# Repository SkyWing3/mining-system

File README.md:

# Mining System

Central de operaciones para la manilla minera: ASP.NET Core 10, MySQL y React 19 + TypeScript y software Python para Raspberry Pi Zero 2 W. La Raspberry Pi 4 puede alojar la central. La interfaz utiliza blanco y la paleta `#DEC1AF`, `#491A06`, `#373946`, `#852A3B`, `#6C4B68`, en modo claro y sin gradientes.

La manilla lee el sensor de CO SEN0564 (mediante un ADS1115) y el termómetro infrarrojo MLX90614, muestra los valores en la OLED, avisa por LED RGB, buzzer y motor vibrador al superar sus umbrales, envía reportes predeterminados y mensajes de voz grabados con el INMP441, y recibe avisos de la central. Las lecturas llegan a la web **en tiempo real** por WebSocket.

## Ubuntu Server LTS con Docker

En la Raspberry Pi 4B con **Ubuntu Server LTS de 64 bits**, Docker y Docker Compose disponibles, ejecutar:

```sh
./start.sh
```

Si Docker requiere permisos de administrador, usar `sudo ./start.sh`. El script compila las imágenes, inicia la API y la web-app, espera sus comprobaciones de salud y muestra la dirección de acceso. Usar el mismo comando para actualizar tras cambiar el código.

Para detener la central conservando los datos: `./start.sh --down` (o `sudo ./start.sh --down`). `./start.sh --help` muestra las opciones.

Abrir **http://franco-rasp4.local**, usando el mDNS del servidor. Nginx redirige ambos WebSockets y la subida de voz; los datos, audios y sesiones se conservan en volúmenes. No hace falta crear `.env` ni instalar Node.js o .NET en el servidor.

Consultar [despliegue Docker](docs/docker.md) para configuración, actualizaciones, respaldos, mDNS y el contenedor opcional de la manilla.

## Desarrollo local

Requisitos: SDK .NET 10, Node.js 22.12+ (o 24+), npm y Python 3.10+ para el dispositivo y las pruebas.

Configurar primero MySQL según [docs/mysql.md](docs/mysql.md). Desde la raíz:

```sh
./scripts/dev.sh
```

Abrir **http://localhost:5173**. La API se ejecuta en **http://localhost:5080**. El primer acceso permite crear el administrador; no hay cuentas ni contraseñas predeterminadas. En accesos posteriores aparece el login. Ctrl+C detiene ambos servicios.

También se pueden iniciar por separado:

```sh
# Terminal 1
ASPNETCORE_ENVIRONMENT=Development dotnet run --project backend/backend.csproj --no-launch-profile

# Terminal 2
cd web-app
npm ci
npm run dev
```

Vite redirige `/api` y `/hubs` a la API para conservar las cookies en el mismo origen. Se puede cambiar el destino con `MINING_API_TARGET`. La configuración privada `launchSettings.json` del SDK puede contener puertos distintos; usar `--no-launch-profile`. Las migraciones se generan con la herramienta local: `dotnet tool restore && dotnet dotnet-ef migrations add Nombre --project backend/backend.csproj`.

## Flujo de uso

1. Crear el administrador desde la pantalla inicial.
2. En **Usuarios**, crear mineros y, si corresponde, supervisores. Las contraseñas tienen un mínimo de 10 caracteres.
3. En **Manillas**, registrar cada dispositivo, su zona y su minero. Cada minero puede tener una manilla activa. Guardar la credencial que se muestra una sola vez.
4. Copiar `device/config/settings.example.json` a `device/config/settings.json` y configurar la dirección de la central y esa credencial.
5. Iniciar el dispositivo o su simulador. Sus lecturas aparecen al instante en **En vivo**.
6. En la OLED, abrir **Mensajes**, seleccionar un reporte y confirmar **Enviar**, o abrir **Voz** para grabar un mensaje.
7. La central recibe el mensaje al instante en **Mensajes**, **Vista general** y, si es crítico, **Alertas**; las grabaciones aparecen en **Voz**.
8. Desde **Avisos** o desde la fila de una manilla se envía un aviso; su estado pasa de Pendiente a Entregado y Leído cuando el minero lo confirma con Enter.

| Rol | Permisos |
| --- | --- |
| Administrador | Monitoreo en vivo, mensajes, voz, avisos, revisión interna de alertas, manillas, gestión de usuarios, actividad y su cuenta. |
| Supervisor | Monitoreo en vivo, mensajes, voz, avisos, revisión interna de alertas, manillas, actividad y su cuenta. |
| Minero | Identidad del portador de la manilla; envía reportes y voz desde el dispositivo. No accede al panel de operaciones. |

Los reportes del menú son predeterminados: **Ayuda**, **Todo bien**, **Hay derrumbe**, **Presencia de gas**, **Compañero herido**, **Necesito evacuar**, **Necesito suministros** y **Saliendo de la mina**. La manilla envía además **Alarma de CO** y **Alarma de temperatura** cuando un sensor entra en peligro, con el valor medido. La web permite buscar (sin distinguir tildes), filtrar y exportar la página actual del historial. Marcar una alerta como revisada registra autor y fecha dentro de la central; no declara resuelto el incidente. Para comunicarse con el minero se usan los **avisos** predefinidos.

## Dispositivo y simulador

```sh
cd device
python3 -m venv .venv
.venv/bin/python -m pip install -r requirements.txt
cp -n config/settings.example.json config/settings.json
# Editar settings.json: connection.url y connection.api_key
.venv/bin/python -m src.main --simulate --config config/settings.json
```

El simulador abre una ventana con la OLED, los botones (flechas y Enter), el LED, el buzzer y el motor. Sus sensores generan lecturas **marcadas como simuladas**; las teclas `g` y `t` fuerzan un pico de CO o de calor para probar las alarmas. La voz simulada es un tono sintético: no usa el micrófono del equipo.

Ejemplo de conexión en la manilla:

```json
{
  "connection": {
    "url": "ws://192.168.1.20:5080/ws/device",
    "api_key": "COPIAR_LA_CREDENCIAL_GENERADA_EN_LA_WEB",
    "heartbeat_seconds": 20,
    "telemetry_seconds": 2,
    "outbox_path": "../state/outbox",
    "voice_outbox_path": "../state/voice"
  }
}
```

Las secciones `sensors`, `alerts` y `voice` son opcionales; sus valores por defecto están en `settings.example.json` y se describen en [OLED, sensores y alertas](docs/hardware/oled-buttons.md). Las rutas de las colas se resuelven respecto al archivo JSON. La URL de subida de voz se deriva de `connection.url` (`ws://host/ws/device` → `http://host/api/device/voice`).

Sin credencial configurada, el menú muestra **Sin configurar** y no declara mensajes enviados. Con credencial, cada mensaje, alarma automática y confirmación de aviso se guarda primero en una cola local de archivos JSON con escritura atómica: **Guardado en cola**. Solo pasa a **Enviado a central** cuando recibe confirmación persistida por el servidor. Si no hay red, permanece en cola y se reintenta al reconectar, incluso después de reiniciar el proceso. El identificador estable evita duplicados. Las grabaciones usan una cola equivalente de archivos WAV.

En hardware:

```sh
GPIOZERO_PIN_FACTORY=lgpio .venv/bin/python -m src.main --config config/settings.json
```

Consultar [OLED, sensores y alertas](docs/hardware/oled-buttons.md), [lista de componentes](docs/componentes.tex), [cableado completo](docs/conexiones.tex) y [diagrama de cableado](docs/imagenes/cableado.png). Para conectar otra Raspberry Pi, servir la central en su interfaz de red: `MINING_BIND_URL=http://0.0.0.0:5080 ./scripts/serve.sh`.

### Manilla con ESP32-S3

[`esp32-device/`](esp32-device/README.md) es el mismo software portado a un ESP32-S3 DevKitC con PlatformIO: mismo menú, alertas, colas y protocolo, sin ADS1115 (el SEN0564 usa el ADC interno). Se configura por la consola serie y la central no necesita cambios.

[`pcb/manilla-portadora/`](pcb/manilla-portadora/README.md) es la placa portadora de doble cara para esa DevKitC: carga y protección de la batería LiPo, elevador a 5 V, LED, pulsadores, buzzer, motor y conectores JST para los módulos. Incluye el paquete de fabricación (Gerbers, lista de compras, planos de montaje y modelo 3D).

## Aplicación compilada

```sh
./scripts/build.sh
./scripts/serve.sh
```

Abrir **http://localhost:5080**: el mismo proceso ASP.NET sirve React, API y ambos WebSockets. No se necesita Vite en producción. `MINING_BIND_URL` cambia la dirección de escucha. Los scripts conservan la base de datos en `data/`.

[Servicio systemd](infra/mining-system.service) y [ejemplo de proxy Nginx](infra/nginx.conf.example) están disponibles para la Raspberry Pi 4. El servicio presupone un usuario `mining`, una instalación en `/opt/mining-system` y .NET en `/usr/bin/dotnet`; adaptar estos valores a la instalación. Para HTTPS, colocar las rutas Nginx dentro del bloque del dominio y su certificado, y usar `wss://` en las manillas. Los encabezados de proxy se aceptan de los proxies locales conocidos por ASP.NET.

## Datos y configuración

- MySQL: usuarios, asignaciones, mensajes, lecturas (con minero, manilla y zona del momento), mensajes de voz, avisos y actividad. Esquema versionado con EF Core, claves foráneas, índices, restricciones `CHECK` y triggers que impiden borrar o alterar el historial. En Docker utiliza el volumen `mysql-data`.
- `data/keys/`: claves persistentes para las cookies; `data/voice/`: grabaciones. Conservar ambas junto a la base de datos al reiniciar o respaldar.
- `device/state/outbox/` y `device/state/voice/`: mensajes y grabaciones aún no confirmados. Datos y secretos quedan fuera de Git.
- `Mining__ConnectionString`: conexión a MySQL; admite contraseña separada mediante `Mining__PasswordFile`.
- `Mining__DataDirectory`: cambia la carpeta de claves de sesión, audios y configuración local del servidor. Fuera de los scripts, la carpeta predeterminada es `../data` respecto al directorio de contenido de ASP.NET.
- `Mining__AllowedOrigins__0`: origen adicional/autorizado para un frontend separado. En el despliegue integrado, el mismo origen funciona automáticamente.
- `Mining__Telemetry__PersistIntervalSeconds` (10): frecuencia de guardado de lecturas; además se guarda cada cambio de nivel, minero o zona. Todas se transmiten en vivo. El historial de lecturas es de solo inserción (ver [MySQL](docs/mysql.md#políticas-de-integridad)).
- `Mining__Voice__MaxBytes`, `Mining__Voice__MaxSeconds`, `Mining__Notices__ExpirationMinutes`, `Mining__PresenceWindowSeconds` y `Mining__LoginAttemptsPerMinute`: límites operativos; se validan al iniciar.
- Docker Compose carga `.env` automáticamente. Los scripts locales no: usar variables de entorno, User Secrets o `/etc/mining-system.env` con el servicio incluido.

Las sesiones usan cookies HttpOnly, SameSite Strict, expiración de ocho horas y contraseñas con hash. Las operaciones de la web requieren el encabezado `X-Mining-Client: web`. Los cambios de contraseña, rol, correo o estado invalidan las sesiones anteriores; las conexiones en vivo también se revocan. Las credenciales de manilla se guardan como hash y se validan en cada evento; renovar la credencial o deshabilitar la manilla cierra su socket en el momento.

## Verificación

```sh
./scripts/test.sh
```

El script compila la API y React, ejecuta las pruebas unitarias .NET, lint, pruebas del dispositivo, pruebas de integración contra MySQL y WebSockets reales, y pruebas de navegador con Playwright. Requiere MySQL y el cliente `mysql`; consultar [configuración y migración](docs/mysql.md). Utiliza bases de datos temporales y no crea usuarios de prueba en `data/`.

Pruebas por separado:

```sh
dotnet build backend/backend.csproj
dotnet test tests/backend.unit
(cd device && .venv/bin/python -m unittest discover -s tests -v)
device/.venv/bin/python -m unittest discover -s tests/backend -v
(cd web-app && npm run build && npm run lint && npm run test:e2e)
```

| Conjunto | Cobertura |
| --- | --- |
| `tests/backend.unit` (xUnit) | Validación WAV, política de guardado de telemetría, límites, catálogos, estados de avisos y jornada de Bolivia. |
| `device/tests` | Configuración y pines, controladores ADS1115/MLX90614, calibración de CO, umbrales con histéresis, LED/buzzer/motor, menú y OLED, colas durables, cliente WebSocket con avisos, grabación y subida de voz, orquestación. |
| `tests/backend` | API real con MySQL: roles, sesiones, asignaciones, idempotencia, telemetría en vivo y guardado limitado, alarmas automáticas, avisos de punta a punta, voz, revocación de sockets. |
| `web-app/tests` (Playwright) | Registro, panel, filtros, alertas, reconexión, lecturas en vivo sin recargar, gráficos, avisos, voz, cuenta y navegación móvil. |

Las pruebas de navegador generan capturas en `web-app/test-results/` (no versionadas).

## Alcance de sensores

La manilla muestrea cada `sensors.sample_seconds` (1 s) y transmite cada `connection.telemetry_seconds` (2 s). La central guarda y difunde temperatura ambiente y de objeto (MLX90614), CO del SEN0564 (en ppm solo con calibración; si no, su tensión) y el nivel de alerta. El circuito no incluye medición de batería: la web lo indica como **Sin sensor**.

El fabricante define el SEN0564 como sensor **cualitativo**. La manilla espera su precalentamiento (`warmup_seconds`) y solo informa ppm con una calibración de dos puntos (`python -m src.tools.calibrate_co`). Sin calibración no se alarma por CO. Los umbrales de precaución y peligro son configurables (por defecto CO 35/200 ppm, ambiente 32/38 °C, objeto 60/90 °C) y deben ajustarse a la normativa y al análisis de riesgos de cada operación; la manilla es un prototipo académico y no reemplaza un detector de gases certificado.

Hardware de la manilla: OLED SSD1306, tres botones, SEN0564 leído mediante un ADS1115, MLX90614, micrófono I²S INMP441, buzzer activo, LED RGB y micro motor vibrador. [Componentes](docs/componentes.tex) describe cada uno y [conexiones](docs/conexiones.tex) asigna sus pines y las pruebas por etapas. Todos los módulos se alimentan a 3,3 V. La configuración rechaza pines repetidos y los GPIO reservados para I²C (2, 3) e I²S (16, 18–21). La validación eléctrica, la calibración y la autonomía deben comprobarse con el montaje físico.

## Estructura

| Carpeta | Contenido |
| --- | --- |
| `backend/` | API ASP.NET Core en capas: `Domain`, `Data` (EF Core y migraciones), `DTOs`, `Services`, `Realtime` (SignalR y WebSocket de manillas), `Workers`, `Controllers`, `Middleware`, `Configuration`. |
| `web-app/` | Central React: `api`, `realtime`, `hooks`, `layout`, `pages`, `components`, `forms`, `styles` y pruebas de navegador. |
| `device/` | Manilla: `sensors`, `alerts`, `audio`, `communication`, `display`, `input`, `tools`, orquestación (`app.py`) y simulador. |
| `esp32-device/` | Manilla en ESP32-S3 (PlatformIO): lógica portable en `lib/core`, controladores y tareas de FreeRTOS en `src`, pruebas nativas en `test`. |
| `pcb/manilla-portadora/` | Placa portadora en KiCad 10, generada con scripts (`tools/`) y paquete de fabricación en `fabricacion/`. |
| `tests/` | Pruebas unitarias .NET, de integración de API/WebSockets y del despliegue Docker. |
| `docs/` | [Contrato de API y tiempo real](docs/api.md), hardware y documentación existente. |
| `scripts/` | Desarrollo, compilación, ejecución y pruebas. |
| `infra/` | Proxy Docker y plantillas de servicio para despliegue. |
| `compose.yaml` | Central Docker: MySQL, backend, web-app y almacenamiento persistente. |
| `compose.device.yaml` | Despliegue Docker opcional de la manilla (OLED, botones, sensores, alertas y micrófono). |

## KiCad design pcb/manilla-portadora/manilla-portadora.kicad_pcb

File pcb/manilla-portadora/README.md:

# Placa portadora de la manilla (v1)

PCB de doble cara para la **ESP32-S3-DevKitC-1 N16R8**. La DevKitC se enchufa en
dos zócalos y la placa agrega:
- la carga y protección de la batería LiPo,
- el elevador a 5 V,
- el LED RGB, los tres pulsadores, el buzzer y la etapa del motor,
- conectores JST XH para los módulos (OLED, MLX90614, SEN0564 e INMP441).

Es la primera versión, pensada para recibir la retroalimentación de **ECROBOTICS** antes de fabricarla.

## Qué entregar al fabricante

`fabricacion/manilla-portadora-gerbers.zip`: Gerbers (RS-274X) de las dos caras
de cobre, máscara, serigrafía y pasta, contorno (`Edge_Cuts`) y taladros Excellon.

| Parámetro | Valor |
| --- | --- |
| Tamaño | 54 × 66 mm, rectangular |
| Capas | 2, FR-4 de 1,6 mm, cobre de 1 oz (35 µm) |
| Máscara y serigrafía | en ambas caras |
| Pista mínima | 0,25 mm (señales); potencia a 0,6 mm |
| Separación mínima | 0,25 mm (entre pads del USB-C y del TP4056: 0,29 mm) |
| Vías | 0,8 mm de diámetro, taladro de 0,4 mm (59 vías) |
| Taladros | 0,40 · 0,60 · 0,80 · 0,90 · 0,95 · 1,00 · 1,10 mm metalizados; 2 de 2,2 mm sin metalizar (montaje M2) |
| Ranuras | 4 ranuras ovaladas metalizadas para las pestañas del USB-C |
| Borde | ningún cobre a menos de 0,5 mm del contorno |

Preguntas para ECROBOTICS:
1. ¿Pueden hacer pistas de 0,25 mm con separación de 0,25 mm?
2. ¿Taladros de 0,4 mm metalizados?
3. ¿Ranuras ovaladas metalizadas? Si no, el USB-C hay que cambiarlo por uno con patas redondas.

## Antes de mandarla a fabricar

- **Medir la DevKitC.** La placa usa la distancia del plano oficial de Espressif:
  22,86 mm entre centros de las dos tiras de pines. Si tu clon mide 25,4 mm, hay que corregir `DEVKIT_X`/`J3_X` en `tools/build_pcb.py`.
- **Confirmar los componentes** de la [lista de compras](fabricacion/lista-de-compras.md):
  - el TP4056 debe ser la versión con almohadilla inferior (ESOP-8);
  - el inductor de 22 µH debe medir 4 × 4 mm.

## Archivos

| Ruta | Contenido |
| --- | --- |
| `manilla-portadora.kicad_pro/.kicad_sch/.kicad_pcb` | Proyecto de KiCad 10 |
| `fabricacion/` | Gerbers en zip, [lista de compras](fabricacion/lista-de-compras.md) y `documentos/` |
| `fabricacion/documentos/` | Esquemático en PDF, planos de montaje de cada cara, BOM en CSV, modelo 3D STEP (para diseñar la carcasa) y vistas |
| `tools/` | Scripts que generan todo lo anterior (ver [Regenerar](#regenerar)) |

## Circuito

**Energía**
- **Entrada:** el USB-C de la portadora (J2) solo carga y alimenta. El TP4056 carga a ~545 mA (R3 = 2,2 kΩ).
- **Protección:** el DW01A con Q1/Q2 corta la batería por sobrecarga, sobredescarga y cortocircuito, porque las LiPo de dron como la ANERA de 1000 mAh suelen venir sin protección.
- **Selección de fuente:** con USB conectado, la manilla toma la energía por D3 y Q3 apaga la batería; sin USB, Q3 conecta la batería.
- **Interruptor:** el de la carcasa va en J10, entre SYS y SYS_ON. Apagado, la batería se sigue cargando.
- **Elevador:** el MT3608 sube a 5,1 V (U3, L1 y D4 juntos y sin vías en el nodo de conmutación) y entra por D5 al pin 5V de la DevKitC, cuyo regulador alimenta los 3,3 V de todo. D5 evita chocar con el USB de la DevKitC: se puede programar con la batería encendida.
- **Medición:** VBAT / 2 en el GPIO 1 y detección de USB en el GPIO 2. El firmware todavía no los usa.

**Mapa de pines**

| Función | GPIO | Función | GPIO |
| --- | --- | --- | --- |
| SEN0564 (ADC1) | 4 | I2C SDA / SCL | 8 / 9 |
| Botones subir / bajar / enter | 5 / 6 / 7 | Motor (AO3400A) | 10 |
| LED R / G / B | 15 / 16 / 17 | INMP441 SCK / WS / SD | 41 / 42 / 40 |
| Buzzer (MMBT3904) | 18 | Batería / USB presente | 1 / 2 |

**Conectores** (JST XH de 2,5 mm; el pin 1 es el cuadrado)

| Conector | Pines | Cara |
| --- | --- | --- |
| J5 OLED | 1 GND · 2 3V3 · 3 SCL · 4 SDA | superior |
| J6 MLX90614 | 1 3V3 · 2 GND · 3 SCL · 4 SDA | superior |
| J7 SEN0564 | 1 3V3 · 2 GND · 3 salida | superior |
| J8 INMP441 | 1 VDD · 2 GND · 3 SD · 4 SCK · 5 WS · 6 L/R (GND) | superior |
| J4 batería | 1 BAT+ · 2 BAT− | inferior |
| J9 motor | 1 + (3V3) · 2 − | inferior |
| J10 interruptor | 1 SYS · 2 SYS_ON | inferior |

La antena de la DevKitC queda sobre una zona sin cobre en las dos caras.

## Firmware para esta placa

El mapa de pines del firmware ya corresponde a esta placa, incluido el
micrófono en los GPIO 41/42/40. Lo único distinto del prototipo en protoboard es
el buzzer: aquí lo maneja un transistor y se activa en alto.

```text
config set {"alerts":{"buzzer":{"active_high":true}}}
```

## Montaje sugerido

1. **Cara inferior, SMD:** protección (U2, Q1, Q2, R8, R9, C3), divisores (R6, R7, R13, R14, C9) y R4/R5.
2. **Cara superior, SMD:** chips, diodos y pasivos. La almohadilla del TP4056 se suelda desde abajo, calentando sus 4 vías.
3. **Conectores de la cara inferior** (J4, J9, J10): se insertan por abajo y se sueldan arriba, antes de los zócalos.
4. **Componentes de agujero de la cara superior:** zócalos J1/J3, conectores de módulos, pulsadores, LED, buzzer y C7/C8.
5. **Antes de enchufar la DevKitC**, con la batería conectada y el interruptor cerrado, medir respecto de GND:
   - unos 5,1 V en el cátodo de D4 (salida del MT3608);
   - unos 4,7 V en el pin 5V del zócalo (J1-21), por la caída de D5.

## Regenerar

Los archivos de KiCad se generan con los scripts y no se editan a mano. Requiere el servidor MCP de KiCad (`uv tool install mcp-server-kicad`) y Java para Freerouting.

```sh
PY=~/.local/share/uv/tools/mcp-server-kicad/bin/python
$PY -I tools/build_schematic.py   # esquemático desde las tablas de componentes y redes
$PY -I tools/build_pcb.py         # huellas, contorno, zonas prohibidas y clases de red
$PY -I -c "from mcp_server_kicad import pcb; pcb.autoroute_pcb(pcb_path='$PWD/manilla-portadora.kicad_pcb', output_dir='$PWD/output/routing', max_passes=40, timeout=900)"
$PY -I tools/finish_pcb.py        # ensancha cuellos, planos GND, rótulos y vías de costura
$PY -I tools/drc_summary.py       # DRC: 0 errores, 0 sin conectar
$PY -I tools/export_fab.py        # paquete de fabricación
```

Al cerrar esta versión, el ERC y el DRC daban **0 errores** y **0 conexiones pendientes**. Solo quedan advertencias de serigrafía: referencias que se tocan con pads vecinos. El fabricante recorta la serigrafía que cae sobre cobre.

## Ideas para la v2

- Llevar los conectores de módulos a la cara inferior para acercar la placa al tamaño de la DevKitC (26 × 63 mm).
- Leer el nivel de batería en el firmware (GPIO 1) y enviarlo a la central, que ya tiene el campo `batteryPercent`.
- Ordenar las referencias de serigrafía en el editor de KiCad.

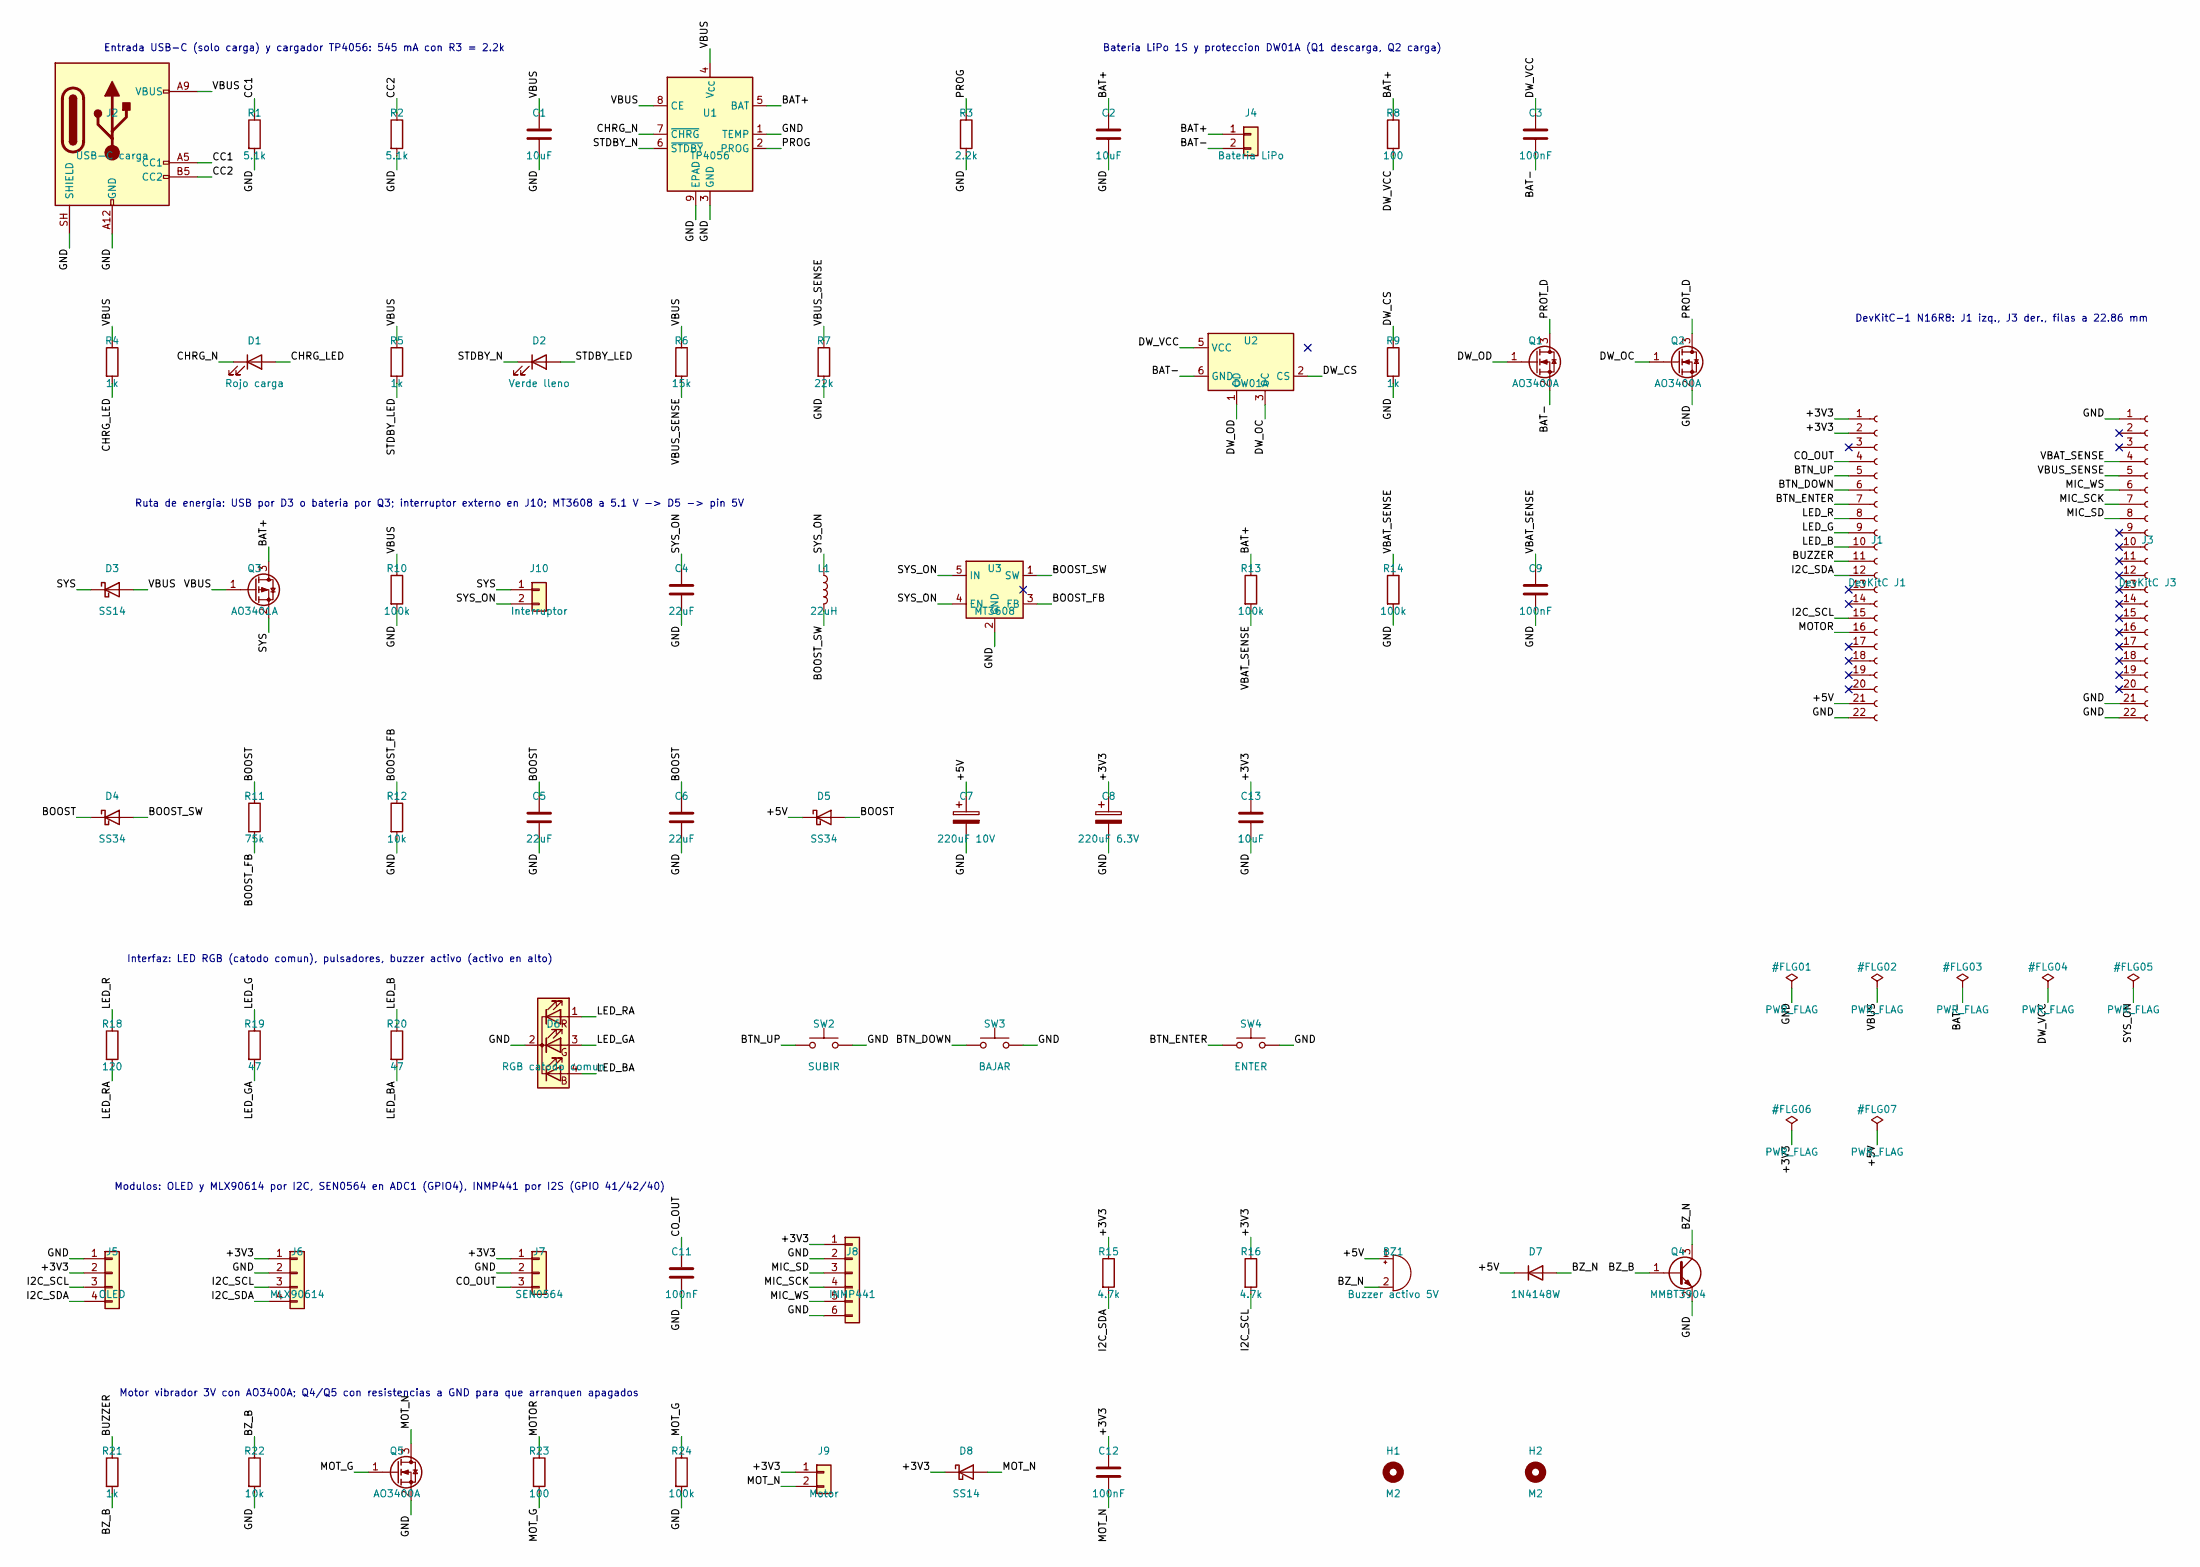
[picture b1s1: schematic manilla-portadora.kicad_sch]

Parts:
BZ1: Buzzer activo 5V; Buzzer_12x9.5RM7.6
C1, C2, C13: 10uF; C_0805_2012Metric
C3, C9, C11, C12: 100nF; C_0805_2012Metric
C4, C5, C6: 22uF; C_1206_3216Metric
C7: 220uF 10V; CP_Radial_D6.3mm_P2.50mm
C8: 220uF 6.3V; CP_Radial_D6.3mm_P2.50mm
D1: Rojo carga; LED_0805_2012Metric
D2: Verde lleno; LED_0805_2012Metric
D3, D8: SS14; D_SMA
D4, D5: SS34; D_SMA
D6: RGB catodo comun; LED_D5.0mm-4_RGB_Staggered_Pins
D7: 1N4148W; D_SOD-123
H1, H2: M2; MountingHole_2.2mm_M2
J1: DevKitC J1; PinSocket_1x22_P2.54mm_Vertical
J2: USB-C carga; USB_C_Receptacle_GCT_USB4125-xx-x_6P_TopMnt_Horizontal
J3: DevKitC J3; PinSocket_1x22_P2.54mm_Vertical
J4: Bateria LiPo; JST_XH_B2B-XH-A_1x02_P2.50mm_Vertical
J5: OLED; JST_XH_B4B-XH-A_1x04_P2.50mm_Vertical
J6: MLX90614; JST_XH_B4B-XH-A_1x04_P2.50mm_Vertical
J7: SEN0564; JST_XH_B3B-XH-A_1x03_P2.50mm_Vertical
J8: INMP441; JST_XH_B6B-XH-A_1x06_P2.50mm_Vertical
J9: Motor; JST_XH_B2B-XH-A_1x02_P2.50mm_Vertical
J10: Interruptor; JST_XH_B2B-XH-A_1x02_P2.50mm_Vertical
L1: 22uH; L_Bourns-SRN4018
Q1, Q2, Q5: AO3400A; SOT-23
Q3: AO3401A; SOT-23
Q4: MMBT3904; SOT-23
R1, R2: 5.1k; R_0805_2012Metric
R3: 2.2k; R_0805_2012Metric
R4, R5, R9, R21: 1k; R_0805_2012Metric
R6: 15k; R_0805_2012Metric
R7: 22k; R_0805_2012Metric
R8, R23: 100; R_0805_2012Metric
R10, R13, R14, R24: 100k; R_0805_2012Metric
R11: 75k; R_0805_2012Metric
R12, R22: 10k; R_0805_2012Metric
R15, R16: 4.7k; R_0805_2012Metric
R18: 120; R_0805_2012Metric
R19, R20: 47; R_0805_2012Metric
SW2: SUBIR; SW_PUSH_6mm
SW3: BAJAR; SW_PUSH_6mm
SW4: ENTER; SW_PUSH_6mm
U1: TP4056; SOIC-8-1EP_3.9x4.9mm_P1.27mm_EP2.41x3.3mm
U2: DW01A; SOT-23-6
U3: MT3608; SOT-23-6

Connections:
/+3V3: C8.1, C12.1, C13.1, D8.1 (K), J1.1, J1.2, J5.2, J6.1, J7.1, J8.1, J9.1, R15.1, R16.1
/+5V: BZ1.1 (+), C7.1, D5.1 (K), D7.1 (K), J1.21
/BAT+: C2.1, J4.1, Q3.3 (D), R8.1, R13.1, U1.5 (BAT)
/BAT-: C3.2, J4.2, Q1.2 (S), U2.6 (GND)
/BOOST: C5.1, C6.1, D4.1 (K), D5.2 (A), R11.1
/BOOST_FB: R11.2, R12.1, U3.3 (FB)
/BOOST_SW: D4.2 (A), L1.2, U3.1 (SW)
/BTN_DOWN: J1.6, SW3.1
/BTN_ENTER: J1.7, SW4.1
/BTN_UP: J1.5, SW2.1
/BUZZER: J1.11, R21.1
/BZ_B: Q4.1 (B), R21.2, R22.1
/BZ_N: BZ1.2 (-), D7.2 (A), Q4.3 (C)
/CC1: J2.A5 (CC1), R1.1
/CC2: J2.B5 (CC2), R2.1
/CHRG_LED: D1.2 (A), R4.2
/CHRG_N: D1.1 (K), U1.7 (~CHRG)
/CO_OUT: C11.1, J1.4, J7.3
/DW_CS: R9.1, U2.2 (CS)
/DW_OC: Q2.1 (G), U2.3 (OC)
/DW_OD: Q1.1 (G), U2.1 (OD)
/DW_VCC: C3.1, R8.2, U2.5 (VCC)
/GND: C1.2, C2.2, C4.2, C5.2, C6.2, C7.2, C8.2, C9.2, C11.2, C13.2, D6.2 (K), J1.22, J2.A12 (GND), J2.B12 (GND), J2.SH (SHIELD), J3.1, J3.21, J3.22, J5.1, J6.2, J7.2, J8.2, J8.6, Q2.2 (S), Q4.2 (E), Q5.2 (S), R1.2, R2.2, R3.2, R7.2, R9.2, R10.2, R12.2, R14.2, R22.2, R24.2, SW2.2, SW3.2, SW4.2, U1.1 (TEMP), U1.3 (GND), U1.9 (EPAD), U3.2 (GND)
/I2C_SCL: J1.15, J5.3, J6.3, R16.2
/I2C_SDA: J1.12, J5.4, J6.4, R15.2
/LED_B: J1.10, R20.1
/LED_BA: D6.4 (BA), R20.2
/LED_G: J1.9, R19.1
/LED_GA: D6.3 (GA), R19.2
/LED_R: J1.8, R18.1
/LED_RA: D6.1 (RA), R18.2
/MIC_SCK: J3.7, J8.4
/MIC_SD: J3.8, J8.3
/MIC_WS: J3.6, J8.5
/MOTOR: J1.16, R23.1
/MOT_G: Q5.1 (G), R23.2, R24.1
/MOT_N: C12.2, D8.2 (A), J9.2, Q5.3 (D)
/PROG: R3.1, U1.2 (PROG)
/PROT_D: Q1.3 (D), Q2.3 (D)
/STDBY_LED: D2.2 (A), R5.2
/STDBY_N: D2.1 (K), U1.6 (~STDBY)
/SYS: D3.1 (K), J10.1, Q3.2 (S)
/SYS_ON: C4.1, J10.2, L1.1, U3.4 (EN), U3.5 (IN)
/VBAT_SENSE: C9.1, J3.4, R13.2, R14.1
/VBUS: C1.1, D3.2 (A), J2.A9 (VBUS), J2.B9 (VBUS), Q3.1 (G), R4.1, R5.1, R6.1, R10.1, U1.4 (V_{CC}), U1.8 (CE)
/VBUS_SENSE: J3.5, R6.2, R7.1

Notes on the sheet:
Entrada USB-C (solo carga) y cargador TP4056: 545 mA con R3 = 2.2k
Bateria LiPo 1S y proteccion DW01A (Q1 descarga, Q2 carga)
Ruta de energia: USB por D3 o bateria por Q3; interruptor externo en J10; MT3608 a 5.1 V -> D5 -> pin 5V
DevKitC-1 N16R8: J1 izq., J3 der., filas a 22.86 mm
Interfaz: LED RGB (catodo comun), pulsadores, buzzer activo (activo en alto)
Modulos: OLED y MLX90614 por I2C, SEN0564 en ADC1 (GPIO4), INMP441 por I2S (GPIO 41/42/40)
Motor vibrador 3V con AO3400A; Q4/Q5 con resistencias a GND para que arranquen apagados

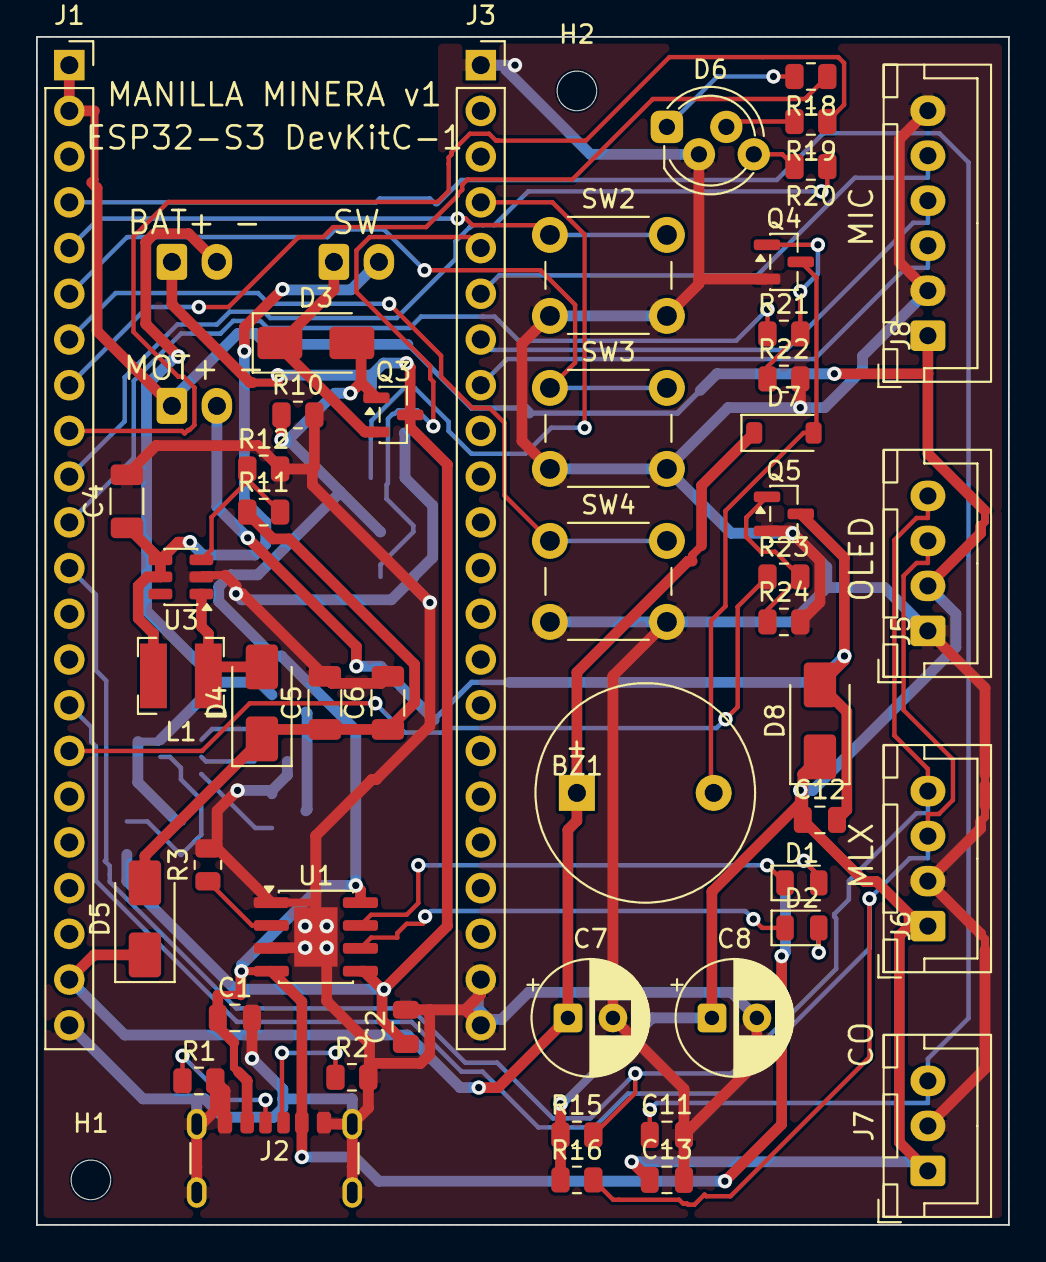
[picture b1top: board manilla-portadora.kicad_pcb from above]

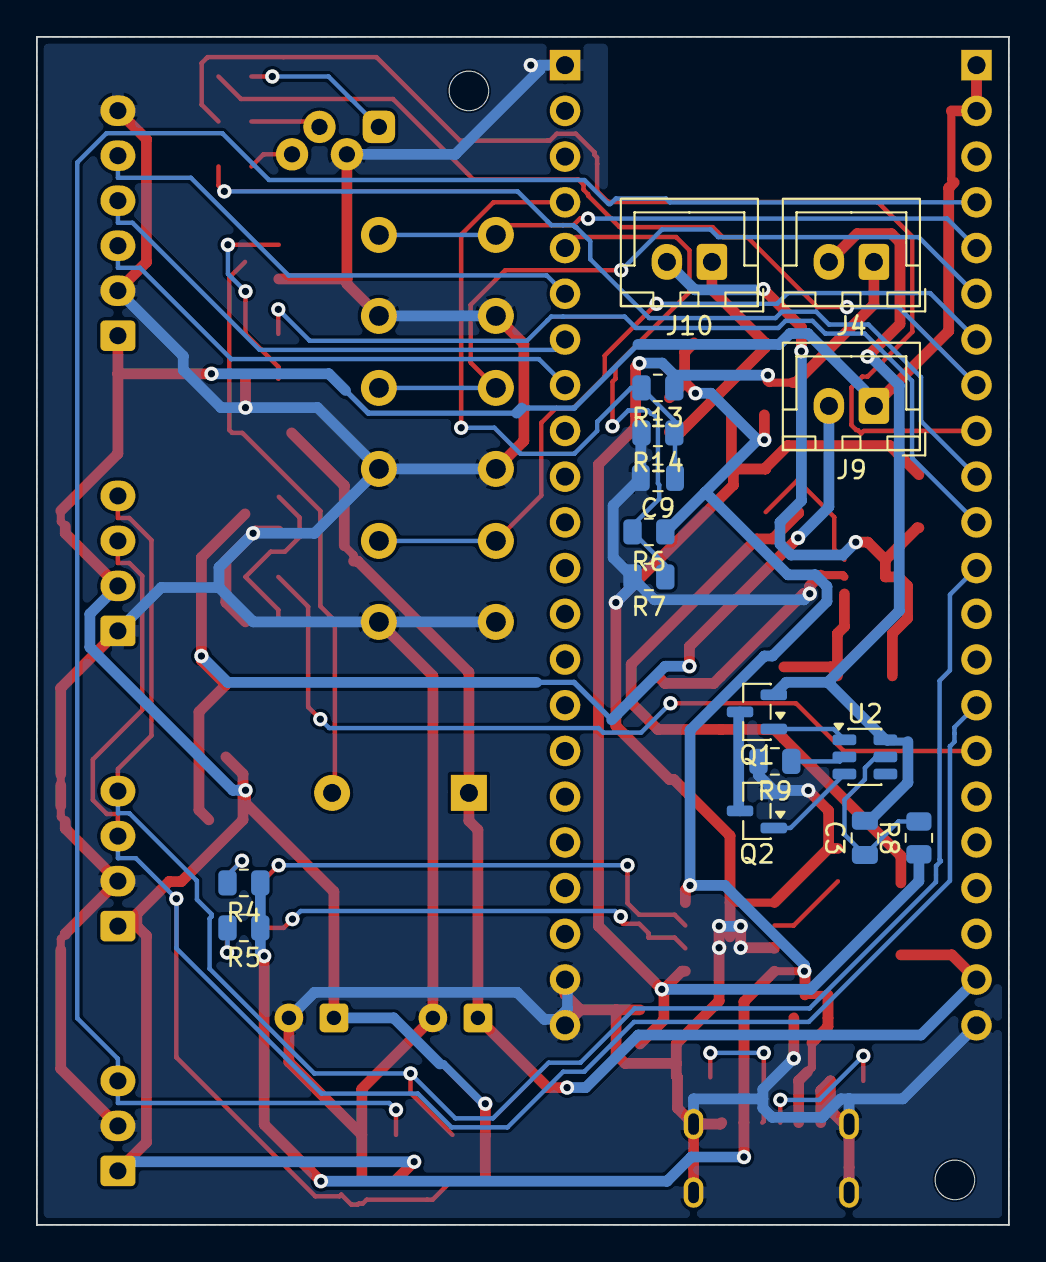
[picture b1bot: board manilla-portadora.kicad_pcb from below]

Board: 2 copper layers, 54.0 x 66.0 mm, 68 parts (16 on the bottom side), 46 nets.

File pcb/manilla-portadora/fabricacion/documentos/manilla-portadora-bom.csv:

"Refs","Value","Footprint","Qty","DNP"
"BZ1","Buzzer activo 5V","Buzzer_Beeper:Buzzer_12x9.5RM7.6","1",""
"C1","10uF","Capacitor_SMD:C_0805_2012Metric","1",""
"C2","10uF","Capacitor_SMD:C_0805_2012Metric","1",""
"C3","100nF","Capacitor_SMD:C_0805_2012Metric","1",""
"C4","22uF","Capacitor_SMD:C_1206_3216Metric","1",""
"C5","22uF","Capacitor_SMD:C_1206_3216Metric","1",""
"C6","22uF","Capacitor_SMD:C_1206_3216Metric","1",""
"C7","220uF 10V","Capacitor_THT:CP_Radial_D6.3mm_P2.50mm","1",""
"C8","220uF 6.3V","Capacitor_THT:CP_Radial_D6.3mm_P2.50mm","1",""
"C9","100nF","Capacitor_SMD:C_0805_2012Metric","1",""
"C11","100nF","Capacitor_SMD:C_0805_2012Metric","1",""
"C12","100nF","Capacitor_SMD:C_0805_2012Metric","1",""
"C13","10uF","Capacitor_SMD:C_0805_2012Metric","1",""
"D1","Rojo carga","LED_SMD:LED_0805_2012Metric","1",""
"D2","Verde lleno","LED_SMD:LED_0805_2012Metric","1",""
"D3","SS14","Diode_SMD:D_SMA","1",""
"D4","SS34","Diode_SMD:D_SMA","1",""
"D5","SS34","Diode_SMD:D_SMA","1",""
"D6","RGB catodo comun","LED_THT:LED_D5.0mm-4_RGB_Staggered_Pins","1",""
"D7","1N4148W","Diode_SMD:D_SOD-123","1",""
"D8","SS14","Diode_SMD:D_SMA","1",""
"H1","M2","MountingHole:MountingHole_2.2mm_M2","1",""
"H2","M2","MountingHole:MountingHole_2.2mm_M2","1",""
"J1","DevKitC J1","Connector_PinSocket_2.54mm:PinSocket_1x22_P2.54mm_Vertical","1",""
"J2","USB-C carga","Connector_USB:USB_C_Receptacle_GCT_USB4125-xx-x_6P_TopMnt_Horizontal","1",""
"J3","DevKitC J3","Connector_PinSocket_2.54mm:PinSocket_1x22_P2.54mm_Vertical","1",""
"J4","Bateria LiPo","Connector_JST:JST_XH_B2B-XH-A_1x02_P2.50mm_Vertical","1",""
"J5","OLED","Connector_JST:JST_XH_B4B-XH-A_1x04_P2.50mm_Vertical","1",""
"J6","MLX90614","Connector_JST:JST_XH_B4B-XH-A_1x04_P2.50mm_Vertical","1",""
"J7","SEN0564","Connector_JST:JST_XH_B3B-XH-A_1x03_P2.50mm_Vertical","1",""
"J8","INMP441","Connector_JST:JST_XH_B6B-XH-A_1x06_P2.50mm_Vertical","1",""
"J9","Motor","Connector_JST:JST_XH_B2B-XH-A_1x02_P2.50mm_Vertical","1",""
"J10","Interruptor","Connector_JST:JST_XH_B2B-XH-A_1x02_P2.50mm_Vertical","1",""
"L1","22uH","Inductor_SMD:L_Bourns-SRN4018","1",""
"Q1","AO3400A","Package_TO_SOT_SMD:SOT-23","1",""
"Q2","AO3400A","Package_TO_SOT_SMD:SOT-23","1",""
"Q3","AO3401A","Package_TO_SOT_SMD:SOT-23","1",""
"Q4","MMBT3904","Package_TO_SOT_SMD:SOT-23","1",""
"Q5","AO3400A","Package_TO_SOT_SMD:SOT-23","1",""
"R1","5.1k","Resistor_SMD:R_0805_2012Metric","1",""
"R2","5.1k","Resistor_SMD:R_0805_2012Metric","1",""
"R3","2.2k","Resistor_SMD:R_0805_2012Metric","1",""
"R4","1k","Resistor_SMD:R_0805_2012Metric","1",""
"R5","1k","Resistor_SMD:R_0805_2012Metric","1",""
"R6","15k","Resistor_SMD:R_0805_2012Metric","1",""
"R7","22k","Resistor_SMD:R_0805_2012Metric","1",""
"R8","100","Resistor_SMD:R_0805_2012Metric","1",""
"R9","1k","Resistor_SMD:R_0805_2012Metric","1",""
"R10","100k","Resistor_SMD:R_0805_2012Metric","1",""
"R11","75k","Resistor_SMD:R_0805_2012Metric","1",""
"R12","10k","Resistor_SMD:R_0805_2012Metric","1",""
"R13","100k","Resistor_SMD:R_0805_2012Metric","1",""
"R14","100k","Resistor_SMD:R_0805_2012Metric","1",""
"R15","4.7k","Resistor_SMD:R_0805_2012Metric","1",""
"R16","4.7k","Resistor_SMD:R_0805_2012Metric","1",""
"R18","120","Resistor_SMD:R_0805_2012Metric","1",""
"R19","47","Resistor_SMD:R_0805_2012Metric","1",""
"R20","47","Resistor_SMD:R_0805_2012Metric","1",""
"R21","1k","Resistor_SMD:R_0805_2012Metric","1",""
"R22","10k","Resistor_SMD:R_0805_2012Metric","1",""
"R23","100","Resistor_SMD:R_0805_2012Metric","1",""
"R24","100k","Resistor_SMD:R_0805_2012Metric","1",""
"SW2","SUBIR","Button_Switch_THT:SW_PUSH_6mm","1",""
"SW3","BAJAR","Button_Switch_THT:SW_PUSH_6mm","1",""
"SW4","ENTER","Button_Switch_THT:SW_PUSH_6mm","1",""
"U1","TP4056","Package_SO:SOIC-8-1EP_3.9x4.9mm_P1.27mm_EP2.41x3.3mm","1",""
"U2","DW01A","Package_TO_SOT_SMD:SOT-23-6","1",""
"U3","MT3608","Package_TO_SOT_SMD:SOT-23-6","1",""
